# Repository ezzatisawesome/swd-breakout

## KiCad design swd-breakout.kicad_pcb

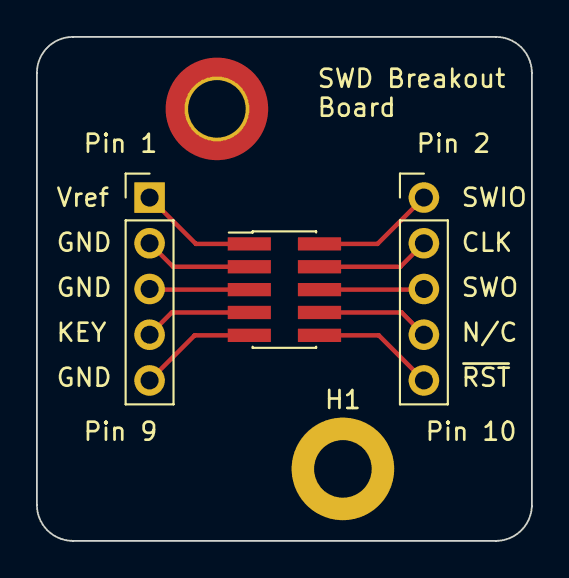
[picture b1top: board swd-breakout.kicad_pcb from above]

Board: 2 copper layers, 27.5 x 28.0 mm, 5 parts (0 on the bottom side), 8 nets.

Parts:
H1: MountingHole; MountingHole_3.2mm_M3_ISO7380_Pad
H2: MountingHole; MountingHole_3.2mm_M3_ISO7380_Pad_TopBottom
J1: Conn_02x05_Odd_Even; PinHeader_2x05_P1.27mm_Vertical_SMD
J2, J3: Conn_01x05_Socket; PinHeader_1x05_P2.54mm_Vertical

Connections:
/CLK: J1.4, J3.2
/GND: J1.3, J1.5, J1.9, J2.2, J2.3, J2.5
/Key: J1.7, J2.4
/SWIO: J1.2, J3.1
/SWO: J1.6, J3.3
/Vref: J1.1, J2.1
/n/c: J1.8, J3.4
/~RST: J1.10, J3.5

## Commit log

2024-10-14 Final commit
2024-10-21 Fixes
2024-10-24 Connecting ground plane to GND pin via net
